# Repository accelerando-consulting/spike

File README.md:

# IoTBNE Garden Spike

This is a project created for the learn-about-circuit-manufacture
workshop, first held in May 2019 for the Brisbane Internet of Things
Interest Group (IoTBNE).

Design and coding is
by [Christopher Biggs](http://christopher.biggs.id.au) and Tim Hadwen
of [Accelerando Consulting](https://accelerando.com.au).  Christopher
is the convenor of IoTBNE.

# About the Project

This project is a computer that lives in your garden, powered by the
sun (it also has a battery which charges during the day, and powers
the computer during the night).

The garden computer is connected to:

* A soil moisture sensor
* A rain/sprinkler sensor
* A temperature sensor
* A humidty sensor
* Your home WiFi
* A server on the internet that shows the measurements on your phone

All these pieces work together to give you a dashboard, right on your
iPhone or Android, of the health of your garden, right now and over
the last few weeks.

We are also going to use this project as an example, to illustrate the
journey from Problem to Product in the Internet of Things.

**What's "The Internet of Things"?**  It's the collection of all the
computers in the world which look after Things, not People.  Our
laptop and desktop computers are for us, their main job is to show
information to our human eyes, I call this The Internet of People.   
Unlike the Internet of People, computers in the Internet of Things are
out of our sight, they talk to each other, and to servers on the
internet, but they don't often talk directly to us.  Our "Internet of
People" computers might talk to the same servers to learn about what
the IoT devices have recorded, or even send them commands.   You could
argue that intelligent systems like Alexa, Siri, Google, Cortana and
friends are bilingual, they are part IoP and part IoT.

# Getting started with the software

We are going to use a programming environment called "Arduino", named
after a pub in Italy where three art teachers met to create a computer
that was intended to allow artists and non-technical creative people
to create art with computers.   The inexpensive Arduino platform was
revolutionary because it allowed people young and old to use sensors
and robotics to widen their world.

## Install the Arduino Integrated Development Environment (IDE)

Humans instruct computers do to things by writing lists of
instructions called **Computer Programs** (or "Software" because the
computer program is an intangible abstract creation, as distinct from
the "Hardware", being the electronics and components that you can
physically touch).  The **art of composing software programs** is called
**Programming**, also known as Coding.

An **Integrated Development Environtment** (IDE) is a program that you
install on your computer which lets you edit computer "**source
code**" (which is the (mostly) human readable part of coding) and then
turn it into "**machine code**" that the computers can understand (but
which is tricky for humans to understand).  This conversion process is
called "**compiling**".  (The I in IDE stands for "Integrated" because
the editor and the compiler used to be separate tools).

Your instructor will provide a USB memory stick with the Arduino IDE
on it.  You can also if you prefer download the Arduino IDE directly
from [the Arduino Download Page](https://www.arduino.cc/en/Main/Software).

## Install the ESP32 Compiler add-on for Arduino.

**Arduino** is both the name of the **software**, and a brand of
computer **hardware**.  The Arduino environment proved so popular that
many other computers (not made by the Arduino company) have also been
enabled to run the Arduino software.

The first Arduino computers used a kind of computer chip called the
"Atmel AVR".  We will be using a different computer which uses a chip
called the "Espressif ESP32".  The ESP32 understands a different
dialect of machine code from that understood by the Atmel AVR, so we
will need to download some extra software to allow the Arduino IDE to
compile our source code into the kind of machine code that the ESP32
understands.

Please follow
[these instructions](https://accelerando.com.au/learn/system-on-chip/esp32/)
to install the ESP32 add-on for Arduino.

## Install the USB drivers for our ESP32 Development board

We will copy our machine code onto the ESP32's internal memory using a
USB cable.  The board will show up as a "COM Port" (aka Serial port)
on your computer when connected.  If it does not show up you will need
to install the drivers for the "CH340" USB device,
using
[these instructions](https://accelerando.com.au/learn/microcontrollers/interfacing/)

# Getting started with the hardware

Now that we have all the software we need, let's make the hardware do
our bidding.

We will begin with the "Brain" of our project, a "Development Board"
called the "TTGO Mini 32".  This board has an ESP32 processor, some
memory, a USB port, a battery charger, and some sockets for attaching
sensors.

In broad terms, a computer consists of a **Central Processing Unit
(CPU)** which processes information, and **peripheral devices** which
provide information about the real world, or turn information into
real-world actions.  The ESP32 microprocessor has a number of built in
peripheral devices.  It has a WiFI radio, a bluetooth radio, some
other communication interfaces and a number of General Purpose Input
Output Pins (GPIOs).   **Digital** IO pins represent the informational
concepts of True and False (or 1 and 0) as a high voltage and a low
voltage respectively.  

A digital GPIO pin can be programmed to **output** either High Voltage (3.3v)
or Low Voltage (0v).  We use this voltage to control outside devices.
A GPIO pin can also be programmed to *sense* voltage, or act as an
**input**, a high voltage will be read as a 1 and a low voltage will
be read as a 0.

In addition to **digital** GPIO pins, the ESP32 also has some
**analog** GPIO pins.  Unlike digital pins which can represent only
the numbers 0 and 1, analog IO pins instead represent (or sense) a
number as a proportional voltage, eg an analog input may treat 0v as
the number 0, 3.3v as the number 4095, and any voltage in between as
the proportionate number in between 0 and 4095.

## Step one: make it blink

We are going to make the built-in Light Emitting Diode (LED) flash on
the board.  This is perhaps the simplest thing you can make a
microprocessor do, and it's traditionally the first program we run on
a new device, just to confirm that everything works.

Let's begin by opening the Arduino IDE.

Now select from the menu bar `File -> Examples -> 01.Basics -> Blink`.
A new window will open containing the **source code** of one of the
Arduino example programs.   This one just makes a light blink.

Many development boards have a built in Light Emitting Diode (LED) for
testing.  Your **TTGO Mini 32** development board has three

	* A red power LED that is always on
	* A blue LED that lights up when the battery is charging
	* A green LED that is connected to the ESP32's "General Purpose
      Input/Output number 22", or GPIO22.   
	  
We are going to modify this blink program to use GPIO22, by adding one
more line after line 24.

```
#define LED_BUILTIN 22
```

Lines 20-30 should thus look like

```
 This example code is in the public domain.

  http://www.arduino.cc/en/Tutorial/Blink
*/

#define LED_BUILTIN 22
// the setup function runs once when you press reset or power the board
void setup() {
  // initialize digital pin LED_BUILTIN as an output.
  pinMode(LED_BUILTIN, OUTPUT);
}

```

What does all this mean?
[You can learn more here](https://accelerando.com.au/learn/microcontrollers/programming/).

Note, when reading the above article, that the original Arduino (with
Atmel AVR microprocessor) has its LED on GPIO13, while our ESP32 uses
GPIO22.

### Compile your first program

Now we have a program, we are going to **Compile** it, that is
translate the **source code** which we wrote (and can read), into
**machine code** which has the same meaning as the source code we
wrote, but is in a form that the computer can understand, and process
the instructions we wrote.

First, we have to tell the Arduino IDE which computer chip we are
using.  Select the `Tools` menu and then `Board`.  You will get a
cascading menu with a lot of names in it.   Look for a section named
"ESP32 Arduino" and select the first option below it "ESP32 Dev
Module".

Select the `Tools` menu again, then `Port`.  Select the Serial Port
that represents the USB interface on your board.   Compare the serial
port list before and after plugging in the board if you are not sure
which one.   You are looking for the new entry that appears after you
connect your board.

Click the 'Compile' button (the tick icon, at the left hand side of
the toolbar).  If your program is valid (makes sense to the compiler),
you will get a successful compilation resulting some machine code.
If your source code is not valid, you will get some error messages,
and welcome to the boundless world of correcting (or "de-bugging")
your program.    Seriously, call for a facilitator to help you if you
are stuck.

Once we have a successful compilation we can copy the machine code to
the memory chip on the board, this is referred to as "Uploading".
Click the Upload button (second icon from the left, a
rightward-pointing arrow).

Watch the status message at the bottom of the source code window.  It
will say "Uploading" and later change to "Upload complete" or "Upload
failed".

If the upload succeeds, watch for the green LED on your board to begin
flashing!   You have compiled and uploaded your first program.

## Step two: install the Spike program

### Download the spike program from GitHub

Now lets install the program that makes our module perform the task we
want, to act as a garden soil sensor.

If you are reading these instructions on Github, look at the top right
of the page for a green button marked "clone or download".   Click it,
then click "Download ZIP".    After the download completes, extract
the downloaded Zipfile. 

Open up the Arduino IDE and choose `File -> Open`.   Look for the
folder you extracted (named spike) and open `spike.ino`.

**Please note**:

* Make sure you download the whole project (as a ZIP file or via `git clone`, **not just** the `spike.ino` file).
* You must rename the folder containing spike.ino and other files to be named `spike` (not, say `spike-master`).

### Install third-party source-code libraries

Spike makes use of some **library source code** written by other authors.
Libraries provide ways to do common tasks without having to build
everything from scratch yourself.  The Arduino system includes a large
number of optional libraries that you can install to control many
kinds of hardware.

In the Arduino IDE select the menu `Sketch -> Include Library -> Manage
Libraries`.   Search for and install the following libraries:

* Blynk
* DHT sensor library for ESPx
* ArduinoJSON (**select version 6.6.0-beta before clicking install**)

The following library is not in the library manager list, and must be
downloaded separately.   On Windows unzip it to Documents/Arduino/libraries.
Location on Mac or Linux may vary, place it where you find the other
libraries (eg search for Blynk after installing it).

* https://github.com/unixbigot/WIFIMANAGER-ESP32/archive/HTTPHEAD.zip

### Run the program (Upload it to your Mini32)

Click the `Upload` button in the Arduino IDE (second from left in the
toolbar, with the rightward-arrow icon).

After the upload completes, click the "serial monitor" button , at the
far right of the toolbar (magnifying-glass icon, or select the menu
`Tools -> Serial Monitor`).

A window should open showing messages from the ESP32.  You should see some messages that look like:

```
IoTBNE Garden Spike, v1 May 2019
#      33 NOTICE void _printWakeReason()(238) ESP Wakeup reason: other
#      33 NOTICE void setup()(186) IO Setup
```

(and many more).

## Step three: get your Spike on the WiFi

Your spike doesn't know the name of your WiFI network, nor your WiFi
password yet.  We could use the USB cable to send it this information
password, or embed it in the source code, but you wouldn't want to
have to go dig up your garden if you change your wifi password.

So our program for the ESP32 will, if it cannot successfully join any
WiFi network, create its own network named "esp_[number]".   When you
join this network from your laptop or phone, it will display a web
page where you can configure which wifi to join, and supply the password.
You can also change some other settings on this page.

This "captive portal" page uses the same mechanism that you may have
encountered in internet cafes or hotel wifi.

Connect your ESP32 to your computer, and open the Arduino Serial
Monitor.

Press the reset switch on your board (look for a tiny button marked
`RST`), and you should see some messages.  Look for a mesage about
having connected to the WiFi and received an IP address.

If the board cannot connect to WiFi it will go back to the access
point mode, and you can connect it to change the settings.   The
message window will contain the name of the hotspot that the device
has created.

If you want to force the board to go into setup mode, unplug any
peripheral shields and connect a jumper lead between GPIO5 and GND,
then reset the board.  It should go into access point mode (you can
then remove the jumper lead).

## Step four: plug in the peripherals

A popular wifi-enabled arduino-compatible development board is named
the "Lolin D1 Mini".  It has 16 pins in two rows and is designed to
connect to "shields" which stack on top of the development board.

Our TTGO Mini32 development board is more powerful than the D1 and has
many more pins, but it is designed to be compatible with the D1's
shields.  The top portion of the inner rows of pins on the TTGO
matches the function of the D1s pins, so that we can plug in D1
shields.

The garden spike project uses a particular Digital Humidity and
Temperature sensor (a module called the DHT11) fitted to a D1 shield.
Next we'll attach this sensor.

### Temperature/Humidity sensor

Your spike does only one job: it powers on, connects to wifi, reads
information from some sensors, transmits the information to a server
on the internet, and then goes to sleep for one minute.   After a
minute it will reboot and repeat the process.   Forever.

But, there are no peripherals attached yet, so the input values won't mean
anything.  Let's attach our first sensor.

Our temperature and humidity sensor peripheral comes on a **shield**
that plugs into the sockets on the dev board.  Make sure you orient it
the correct way around (look for the pins marked RST at the top of the
shield and align it with the socket market RST on the TTGO development
board.

Plug your spike back in, and open up the Arduino serial monitor.  When
the board prints "SENSORS" you should see the temperature and humidity
values start to make sense.

### Let's make a dashboard with "Blynk"

We are now going to use a free phone app called "**Blynk**" to view the sensor
values.   Our board will transmit the readings to Blynk's servers, and
our app will fetch them from the same server.

Begin by searching your phone's app store for the Blynk application.
Create an account which will allow you to host your own dashboards.

#### Import the Spike dashboard into your Blynk App

Open the Blynk app on your phone.  **Make sure you log in**.  Now tap
the "Scan QR" code icon in the blynk toolbar and scan this code.  This
will create a copy of the Spike Application.

Blynk allows simple apps to be created for free.  For more complex
apps extra widgets may be purchased via in-app purchase.   You can
scan the code below to obtain a more complex app, but you may have to
spend a couple of dollars to unlock extra widgets.

#### Configure your device to connect to your application

In Blynk, tap the hexagonal "settings" icon, and look for a section
marked "auth token".  Tap 'email' to email the token to yourself.

Now we need to type that token into your Dev Board's settings.
Connect GPIO5 to GND and reboot your board.   Join your board's WiFi
network and, when the settings page is shown, enter the auth token
value into the corresponding box on the settings page.

Have a look at the other settings; you should give your device a
unique name, for example, this will be used when we later upload
programs to your device "Over The Air" (via wifi instead of using a
USB cable).

Back on your phone, click the "Play" icon to start the app.   Now
reboot your development board.   Within a minute you should see the
temperature and humidity value appear on your phone.

We have made our first IoT dashboard app.

### Connect more sensors

We have two more sensors to connect, a rain sensor and a soil moisture
sensor. 

## Oh wait, we ran out of sockets!

But where do we connect them?    The DHT shield is blocking the sockets.

The D1 shield system is designed to allow shields to stack on top of
each other, using special components that have a pin below the board and a
socket above it.   But our DHT shield has only pins, no sockets.
This is because we want it to be the "top" of the stack.   We must fit
our other devices underneath it.

But there is no "soil sensor shield" available to buy for the D1
system, nor a "rain sensor shield".  So we made one.  We call it
"Frankenshield".  It isn't pretty.

In fact, we made the shield deliberately ugly to prove a point.   When
you are at the proof of concept stage, you want rapid validation, so
you do the simplest thing that could possibly work, no matter how
ugly.    Beauty will come later.

The Frankenshield is made using "Veroboard" which has a grid of holes 
with copper tracks running the length of the board.   This allows us
to create "one off" circuit boards by cutting and joining the tracks
as needed.   Before creating printed circuit boards became cheap,
quick and easy, various kinds of "prototyping boards" were commonly
used for, well, prototypes.

Later in this workshop we will design a Printed Circuit Board (PCB) to
replace the Frankenshield.

### Connecting the FrankenShield

The "Frankenshield" connects at the bottom of the D1 socket, using
many of the same pins as the DHT sheild.  It also uses some of the
pins in the outer row.   These are special Analog input pins, which
allow us to sense the voltage output from the sensors.

The Arduino environment has a built in procedure called `analogRead`
which returns a number representing the voltage present on an analog input
pin.  A voltage of 0v corresponds to the number zero, and a voltage of
3.3v corresponds to the number 4095 (4095 is the largest number that can be
represented with 12 **binary digits**, or **bits** for short, thus we say
the ESP32's analog input has a "12-bit precision"). 

### The rain sensor

The rain sensor connects to the two pins on the left hand side of the
Frankenshield.  **It does not matter which way around the sensor is
connected.**

**Warning: Science Content**: the following paragraph discusses
**electrical resistance**.  If you are new to electronics, you can
learn more about the basic concepts we will
discuss [here](https://accelerando.com.au/learn/basics/).   You can
safely skip the next paragraph if you do not want to know the details.

The rain sensor printed circuit board consists of two copper tracks
which are closely spaced but not connected.   We connect one track to
3.3v and the other to the analog input pin.   We also connect the
analog input pin to 0v via a **resistor**.   The resistor makes the
voltage at the input pin "want" to be zero volts, but the particular resistor has
we use has very high resistance, so we refer to this as a "weak
pull-down resistor".   When something bridges the tracks on the rain
sensor board, this constitutes a lower resistance than the pull-down,
so voltage on the input pin is "pulled up" to somewhere between zero
and 3.3 volts.   This results in an `analogRead()` call for the input
pin returning a number between 0 and 4095.    When the rain sensor is
perfectly dry and clean, we expect it to read as 0; when rain falls,
the value read will be higher. 

To read the rain sensor we call `analogRead()`, which returns a number
between 0 and 4095 representing the input voltage, then we **scale** the
number, so instead of being between 0 and 4095 it is between 0
and 100.   You can think of this reading as "X percent rainy".

### The soil-moisture sensor

It is possible to sense soil moisture in the same way, using a spiked probe
with copper tracks and measuring the soil resistance, but the presence
of voltage in the complex soil environment causes chemical reactions
which can corrode the probe.

**Warning: Science Content**.   You can safely skip the 
next paragraph if you do not want to know the details.

Instead we use a more complex **Capacitive** sensor, which is
insulated from the soil by a layer of paint.   The dampness of the
soil effects its **conductivity**, if we apply an electric charge to
the insulated probe, the charge can "leak" away via the
electromagnetic field created in the slightly conductive soil.
Measuring the rate at which charge leaks away allows us to infer the
dampness of the soil without actually touching it.

Like the soil sensor, to read the rain sensor we call `analogRead()`,
which returns a number between 0 and 4095 representing the input
voltage.  However the soil sensor will return 4095 in perfectly dry
soil, and a lower number in damp soil.  We subtract the result from
4095 to "invert it", then we scale the number again, so instead of
being between 4095 (dry) and 0(wet) it is between 0 (dry) and 100
(wet).  You can thus think of this reading as "X percent damp".

The soil sensor is an **active sensor**, which means we must give it
power to operate the electronic circuit built into the probe.   The
probe has 3 wires: 

  * Red - Power (3.3volts)
  * Black - Ground (0 volts)
  * Yellow - output voltage (this will
carry a voltage that varies between 0v and 3.3v depending on soil
moisture level).   

We use a 4-pin connector with one pin removed, which makes it
assymetrical; while not strictly necessary, this is a convenient way
to prevent connecting the sensor "backwards".

On the frankenshield there are three pins at the right with one
separated.

The two pins at left are for Power (L) and Ground (R).   The single
pin on the right is for the yellow wire.

You will need to remove the three sockets wires from the black
housing, by lifting up the little black spring tabs on the housing and
then gently tugging on the wire.   Your kit includes a four-pin
housing into which you can insert the three sockets, leaving a gap to
match the gap in the pins.   

### The hidden third sensor - battery voltage

Many battery powered development boards connect the battery to one of
the analog pins to allow the CPU to measure the battery voltage,
giving the system the capability to send an alert (or shut down) when
the battery is going flat.    Unfortunately, our TTGO Mini32 does not
have this arrangement.   So the Frankenshield also provides this.
Fortunately, the 5v socket on the TTGO is also connected to the battery,
so the frankenshield can access the battery voltage through the shield pins.

**Warning: Science Content**.   You can safely skip the 
next paragraph if you do not want to know the details.

The analog input pins on the ESP32 can read a voltage between 0 and
3.3 volts.  Connecting a voltage higher than 3.3 volts can damage the
pins.  But our battery is a **Lithium Ion** battery which measures 4.2 volts
when full (and around 2.9 volts when "flat").   To safely measure the
battery voltage, we **divide** it using a **voltage divider**.   We
take two resistors of equal resistance.   We connect one to the
positive terminal of the battery (4.2v) and the other to the negative
(0v).  We join the other ends of the two resistors together.   We
choose a fairly high resistance so that only a small current flows, so
as not to waste the battery.   If we measure the voltage at the
junction of the two resistors, it will be half of the battery
voltage.   If we connect that junction to an analog input pin, a
reading of 0 will mean 0 volts, and a reading of 4095 (a measured
voltage of 3.3v) would mean that the battery voltage was 6.6v.

To read the battery voltage, we call analogRead() on the pin 
which is connected to the battery via a voltage-divider, giving half
of the battery voltage.   We multiply the analog reading by `6.6/4095`, giving
us a a number equal to the battery voltage.

Your battery plugs into a small beige socket on the underside of the
TTGO board.

### Putting it all together

Let's assemble our contraption.  Plug the frankenshield into the TTGO
development board, being careful to align the pins.  Now plug the DHT
shield into the frankenshield.  Connect the battery to your TTGO
board, and turn on the power switch.

You should see the red power light turn on.   After a few seconds the
green LED should blink, this indicates that the Arduino `loop()` procedure has
been run.   Our loop procedure does five things:

1. Flash the green LED
2. Read the analog input pins connected to Frankenshield
3. Read the temperature and humidity from the DHT sheield
4. Transmit the values to the Blynk servers on the internet
5. Set a wake-up timer, and go into "deep sleep" mode

When the timer goes off, the board will "wake up" and repeat the
above steps, for as long as the battery lasts.

When the ESP32 goes into "deep sleep" it turns off the WiFi and other
high-power-use components, and uses only a trickle of current.
Without the deep sleep, the ESP will consume approximately 0.1 Amperes
of current (100mA), and the battery would run flat in just a few
hours.  By using deep sleep to reduce our power needs, we can extend
our battery life without recharging to a week or more.  By charging
the battery each day via our solar panel, we can realise almost
indefinite battery life.

# Oh yuck, how do we replace that Franken-Shield?

When it was popularised after World War Two, the Printed Circuit Board
revolutionsed electronics, taking it from a world of hand-assembled
Franken-Shields to an assembly line of (now) robot-assembled identical
devices.

If you're at the the IoTBNE workshop, then you are sitting in the
facility of our hosts, Masters and Young, one of Brisbane's most
advanced circuit design and assembly businesses.

Some businesses make just circuit boards, some just do assembly, some
do both.  There are manufacturing services to suit every budget, from
the hobbyist with just $5 to spend, to advanced scientific and
military applications with exacting requirements quality and
robustness.

For the experimenter and hobbyist the process of moving from "jumble
of wires" to "professional product" looks like this

1. Sketch out a **schematic diagram** of the electronic circuit you want to make
2. Use a **schematic capture** program on your computer to create a
   digital representation of your circuit, its connections and the
   components that comprise it.
3. Use a **circuit board layout** program to turn your schematic into
   a diagram of the multiple layers of tracks, holes, cuts and protective/informational
   paint layers that will comprise your Printed Circuit Board.
4. Send your board layout to a PCB Manufacturing Service
5. Either assemble the components onto the returned board yourself, or
   pay extra to have the manufacturing service do this.

## Install the necessary software

There are many **Electronic Design Automation** (EDA) software
products available, costing anywhere from zero to tens of thousands of
dollars.   We are going to choose one of the "zero" options today.

We will be using the **KiCad** suite, which is popular in hobbyist and
enthusiast circles, though it lacks some features that some would
consider essential.

Begin by downloading the installation files from
the [KiCad download page](http://www.kicad-pcb.org/download/).
Your instructor will also have a USB memory stick with the files
already downloaded.

The KiCad suite consists of a number of separate programs, including

1. The KiCad project manager (the "main tool" that launches the
   others)
2. A schematic-capture program named **eeschema**
3. A PCB layout program named **pcbnew** (I'm sorry, engineers have
   less than sparkling taste when naming things).
4. A file-viewer that understands displays the "Gerber" files needed
   by the manufacturing robots, named **gerbview** (are you seeing a
   pattern?).

## Install some component libraries

The process of creating (or "capturing") your schematic diagram
is essentially three steps

1. Drag and drop the components from a **component library** onto your
   page
2. Arrange the components in a way that makes logical sense to you
3. Draw "wires" between the components

The layout of the components on your schematic diagram need not bear
any resemblance to how you will place them on the PCB.  Sometimes it
makes sense to arrange them similarly to how they will sit in the real
world, sometimes not.

The KiCad suite comes with a large component library that contains
"symbols" and "footprints" for many common components.   But it does
not contain the "footprint" (the exact physical dimensions of the
copper pads that will hold the component) for a D1 Shield socket.

KiCad contains tools to create your own symbols and footprints, and as
you journey into the world of circuits you will accumulate your own
library of components that you have created to suit your needs.

However, the Internet is a wonderful place, and Open Source is magic, 
so somebody else has already created the component we will need and
made it freely available.   We are going to use the component designed
by [Raoul Rubien, here](https://github.com/rubienr/wemos-d1-mini-kicad).

This design has already been downloaded and added to this project, but
in general, when faced with a component for which you do not have a
symbol, search the internet first before undertaking to create your
own symbol.

# Let's design an Electronic Circuit

The Spike repository contains some example projects. 

1. A blank project containing just the pins for a "D1 Shield"
2. A project contaning all the parts of the Frankenshield
3. An example of a completed "FrankenShield 2.0"

Open up the first of these, the "`shield-blank`" project.

You should see the project manager page, which lists the documents
that are part of the `shield-blank` project.

Click on the icon for the schematic file, `shield-blank.sch`.

# Let's design a Printed Circuit Board (PCB)

# Let's get our PCB made

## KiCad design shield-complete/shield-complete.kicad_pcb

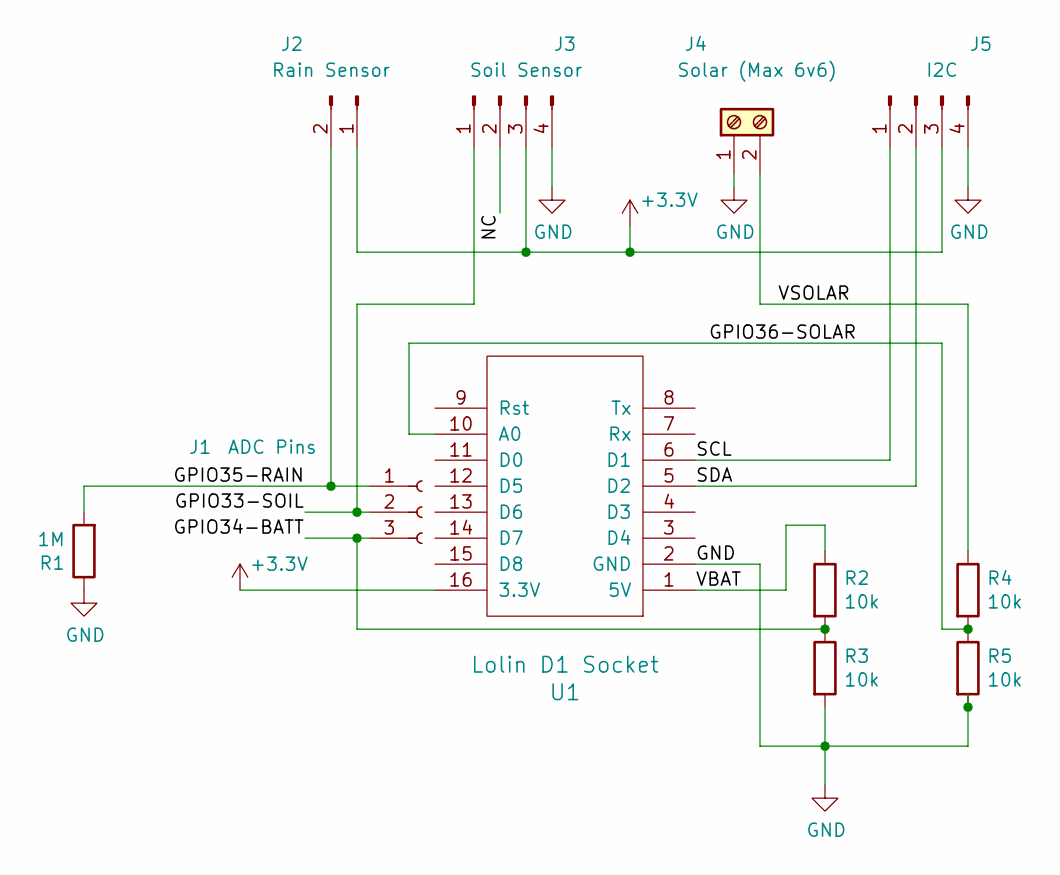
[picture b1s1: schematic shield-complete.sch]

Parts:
J1: ADC Pins; Pin_Header_Straight_1x03_Pitch2.54mm
J2: Rain Sensor; Pin_Header_Straight_1x02_Pitch2.54mm
J3: Soil Sensor; Pin_Header_Straight_1x04_Pitch2.54mm
J4: Solar (Max 6v6); Pin_Header_Straight_1x02_Pitch2.54mm
J5: I2C; Pin_Header_Straight_1x04_Pitch2.54mm
R1: 1M; R_0603_HandSoldering
R2, R3, R4, R5: 10k; R_0603_HandSoldering
U1: Lolin D1 Socket; wemos-d1-mini-with-pin-header-and-connector-no-outline

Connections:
+3V3: J2.1, J3.3, J5.3, U1.16 (3.3V)
/GPIO33-SOIL: J1.2, J3.1
/GPIO34-BATT: J1.3, R2.2, R3.1
/GPIO35-RAIN: J1.1, J2.2, R1.2
/GPIO36-SOLAR: R4.2, R5.1, U1.10 (A0)
/NC: J3.2
/SCL: J5.1, U1.6 (D1)
/SDA: J5.2, U1.5 (D2)
/VBAT: R2.1, U1.1 (5V)
/VSOLAR: J4.2, R4.1
GND: J3.4, J4.1, J5.4, R1.1, R3.2, R5.2, U1.2 (GND)

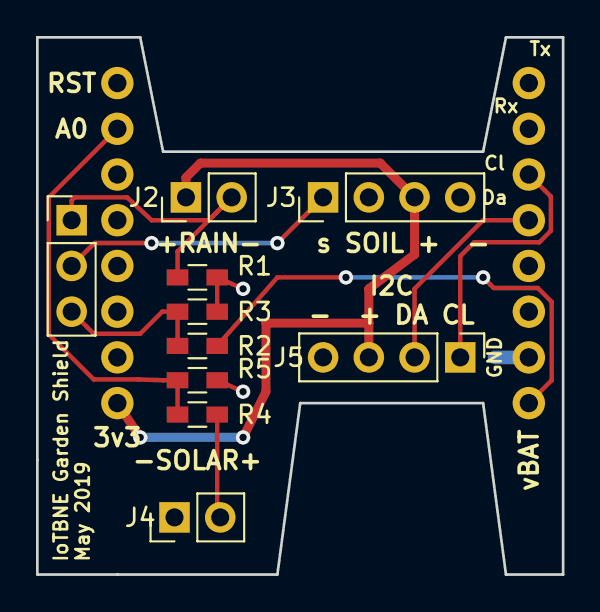
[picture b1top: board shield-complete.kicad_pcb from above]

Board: 2 copper layers, 29.2 x 29.8 mm, 11 parts (0 on the bottom side), 10 nets.

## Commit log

2019-05-07 ESP32 Garden soil monitor
2019-05-10 add README, refine code and enclosure
2019-05-10 More readme
2019-05-10 Example kicad projects
2019-05-12 Documentation updates
2019-05-12 Rename image
2019-05-12 More documentation
2019-05-12 Correct names for QR code images
2019-05-12 Clarify blynk instructions
2019-05-26 Use getLocalTime for trace
2019-05-26 Add Makefile and gitignore files
2019-05-26 Shield as sent for manufacture
2019-05-26 Improve fit of spike lid and rain tongue
2019-05-26 Track light level via solar panel voltage. Fetch time from NTP
